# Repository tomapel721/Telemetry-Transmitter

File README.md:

## :book: Long story short
The transmitter part of telemetry system which was implemented inside a Formula Student EV.

## :computer: How it works - technologies
PCB Design: **KiCad**

Project source code: **C (C18) with usage of HAL libraries**
Board used: **STM32L432KC**

## :file_folder: Repository structure
In main directory, you can find 2 folders:
- directory **PCBDesign** contains project of printed circuit used as HW part of the telemetry transmitter
- directory **SourceCode** contains the SW part of the project

## :scroll: How to use my code
Usage of the code can be hard to do, but in case you want to make your own racing car, here is the brief manual:
1. Print the PCB using the _GERBER_ files
2. Solder the board elements
3. Connect soldered electronics to PC
4. Flash the STM32 using ST-LINK debugger (pins where to connect are marked on the PCB schema)
5. Enjoy;)

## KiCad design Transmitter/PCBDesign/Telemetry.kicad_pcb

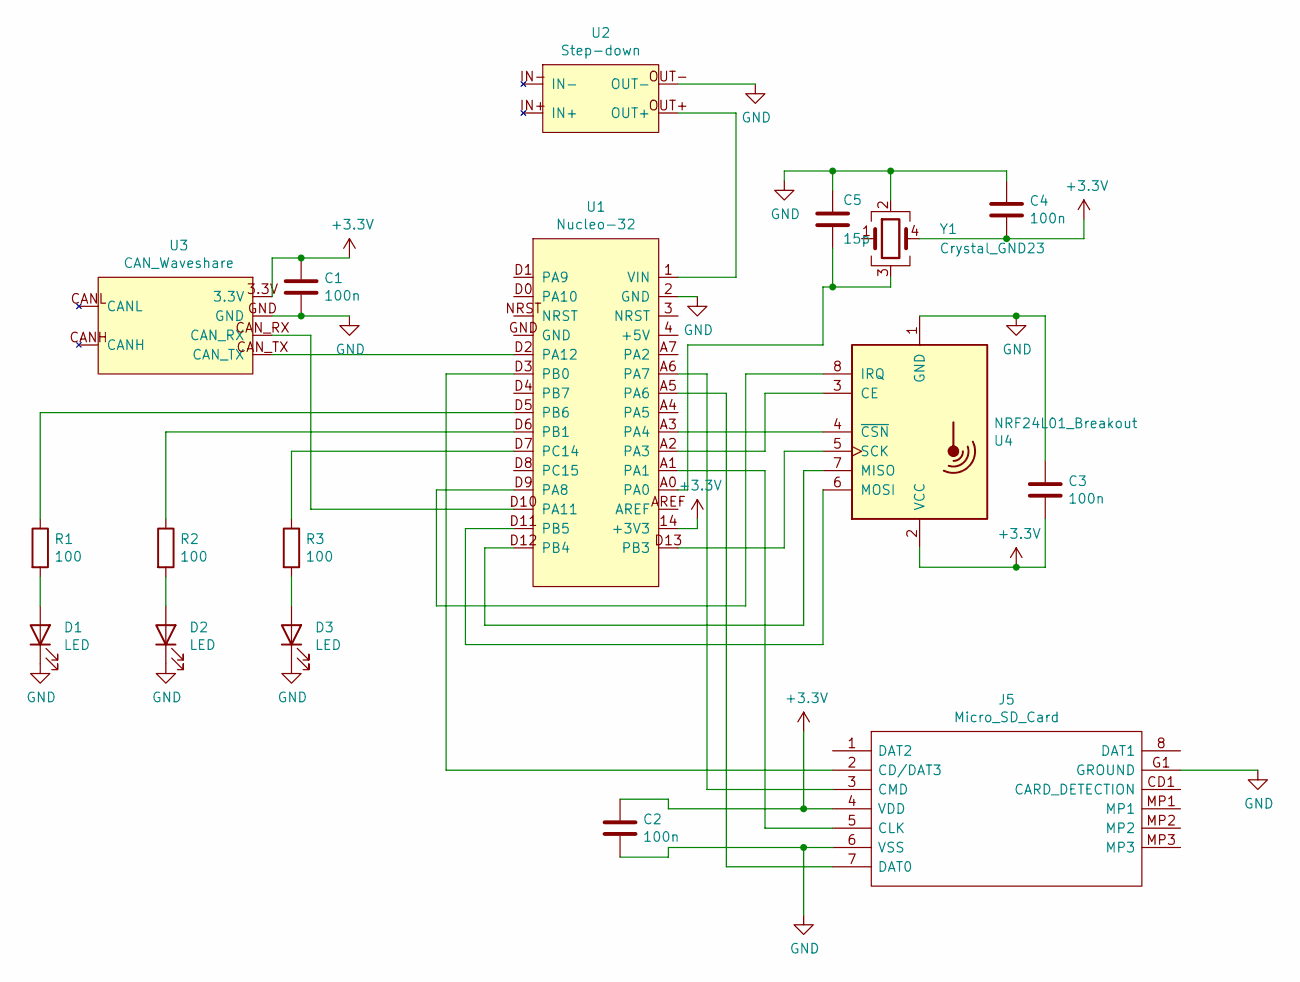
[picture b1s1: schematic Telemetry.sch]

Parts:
C1, C2, C3, C4: 100n; C_0805_2012Metric
C5: 15p; C_0805_2012Metric
D1, D2, D3: LED; D_0805_2012Metric_Pad1.15x1.40mm_HandSolder
J5: Micro_SD_Card; 112JTDARR01; Manufacturer_Part_Number 112J-TDAR-R01
R1, R2, R3: 100; R_0805_2012Metric_Pad1.20x1.40mm_HandSolder
U1: Nucleo-32; Arduino_Nano
U2: Step-down; TerminalBlock_RND_205-00012_1x02_P5.00mm_Horizontal
U3: CAN_Waveshare; PinHeader_1x04_P2.54mm_Vertical
U4: NRF24L01_Breakout; nRF24L01_Breakout
Y1: Crystal_GND23; Crystal_SMD_7050-4Pin_7.0x5.0mm

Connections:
+3V3: C1.1, C2.1, C3.2, C4.2, J5.4 (VDD), U1.14 (+3V3), U3.3.3V, U4.2 (VCC), Y1.4
GND: C1.2, C2.2, C3.1, C4.1, C5.1, D1.1 (K), D2.1 (K), D3.1 (K), J5.6 (VSS), J5.G1 (GROUND), U1.2 (GND), U2.OUT-, U3.GND, U4.1 (GND), Y1.2
unnamed: C5.2, U1.A0, Y1.3
unnamed: D1.2 (A), R1.2
unnamed: D2.2 (A), R2.2
unnamed: D3.2 (A), R3.2
unnamed: J5.2 (CD/DAT3), U1.D3 (PB0)
unnamed: J5.3 (CMD), U1.A6 (PA7)
unnamed: J5.5 (CLK), U1.A1
unnamed: J5.7 (DAT0), U1.A5 (PA6)
unnamed: R1.1, U1.D5 (PB6)
unnamed: R2.1, U1.D6 (PB1)
unnamed: R3.1, U1.D7 (PC14)
unnamed: U1.1 (VIN), U2.OUT+
unnamed: U1.A2 (PA3), U4.3 (CE)
unnamed: U1.A3 (PA4), U4.4 (~CSN)
unnamed: U1.D2 (PA12), U3.CAN_TX
unnamed: U1.D9 (PA8), U4.8 (IRQ)
unnamed: U1.D10 (PA11), U3.CAN_RX
unnamed: U1.D11 (PB5), U4.6 (MOSI)
unnamed: U1.D12 (PB4), U4.7 (MISO)
unnamed: U1.D13 (PB3), U4.5 (SCK)

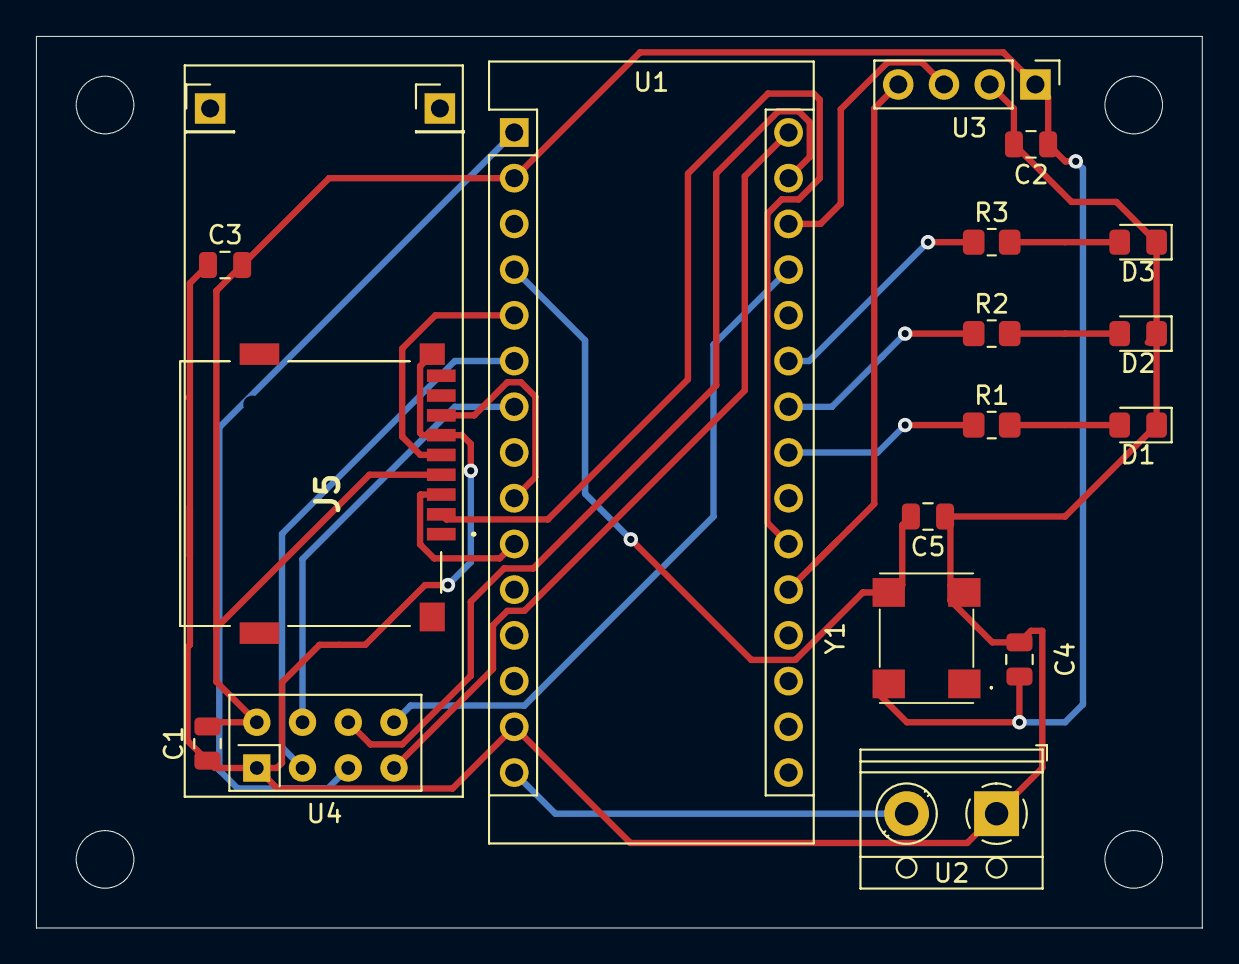
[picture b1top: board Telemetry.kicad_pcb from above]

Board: 2 copper layers, 64.8 x 49.5 mm, 23 parts (0 on the bottom side), 22 nets.

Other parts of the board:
 : .; PinHeader_1x01_P2.54mm_Vertical
 #2: .; PinHeader_1x01_P2.54mm_Vertical
 #3,  #4,  #5,  #6: M3; MountingHole_3.2mm_M3_DIN965

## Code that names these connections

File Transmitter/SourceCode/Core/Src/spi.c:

/**
  ******************************************************************************
  * @file    spi.c
  * @brief   This file provides code for the configuration
  *          of the SPI instances.
  ******************************************************************************
  * @attention
  *
  * <h2><center>&copy; Copyright (c) 2021 STMicroelectronics.
  * All rights reserved.</center></h2>
  *
  * This software component is licensed by ST under Ultimate Liberty license
  * SLA0044, the "License"; You may not use this file except in compliance with
  * the License. You may obtain a copy of the License at:
  *                             www.st.com/SLA0044
  *
  ******************************************************************************
  */

/* Includes ------------------------------------------------------------------*/
#include "spi.h"

/* USER CODE BEGIN 0 */

/* USER CODE END 0 */

SPI_HandleTypeDef hspi1;
SPI_HandleTypeDef hspi3;

/* SPI1 init function */
void MX_SPI1_Init(void)
{

  /* USER CODE BEGIN SPI1_Init 0 */

  /* USER CODE END SPI1_Init 0 */

  /* USER CODE BEGIN SPI1_Init 1 */

  /* USER CODE END SPI1_Init 1 */
  hspi1.Instance = SPI1;
  hspi1.Init.Mode = SPI_MODE_MASTER;
  hspi1.Init.Direction = SPI_DIRECTION_2LINES;
  hspi1.Init.DataSize = SPI_DATASIZE_8BIT;
  hspi1.Init.CLKPolarity = SPI_POLARITY_LOW;
  hspi1.Init.CLKPhase = SPI_PHASE_1EDGE;
  hspi1.Init.NSS = SPI_NSS_SOFT;
  hspi1.Init.BaudRatePrescaler = SPI_BAUDRATEPRESCALER_32;
  hspi1.Init.FirstBit = SPI_FIRSTBIT_MSB;
  hspi1.Init.TIMode = SPI_TIMODE_DISABLE;
  hspi1.Init.CRCCalculation = SPI_CRCCALCULATION_DISABLE;
  hspi1.Init.CRCPolynomial = 7;
  hspi1.Init.CRCLength = SPI_CRC_LENGTH_DATASIZE;
  hspi1.Init.NSSPMode = SPI_NSS_PULSE_ENABLE;
  if (HAL_SPI_Init(&hspi1) != HAL_OK)
  {
    Error_Handler();
  }
  /* USER CODE BEGIN SPI1_Init 2 */

  /* USER CODE END SPI1_Init 2 */

}
/* SPI3 init function */
void MX_SPI3_Init(void)
{

  /* USER CODE BEGIN SPI3_Init 0 */

  /* USER CODE END SPI3_Init 0 */

  /* USER CODE BEGIN SPI3_Init 1 */

  /* USER CODE END SPI3_Init 1 */
  hspi3.Instance = SPI3;
  hspi3.Init.Mode = SPI_MODE_MASTER;
  hspi3.Init.Direction = SPI_DIRECTION_2LINES;
  hspi3.Init.DataSize = SPI_DATASIZE_8BIT;
  hspi3.Init.CLKPolarity = SPI_POLARITY_LOW;
  hspi3.Init.CLKPhase = SPI_PHASE_1EDGE;
  hspi3.Init.NSS = SPI_NSS_SOFT;
  hspi3.Init.BaudRatePrescaler = SPI_BAUDRATEPRESCALER_32;
  hspi3.Init.FirstBit = SPI_FIRSTBIT_MSB;
  hspi3.Init.TIMode = SPI_TIMODE_DISABLE;
  hspi3.Init.CRCCalculation = SPI_CRCCALCULATION_DISABLE;
  hspi3.Init.CRCPolynomial = 7;
  hspi3.Init.CRCLength = SPI_CRC_LENGTH_DATASIZE;
  hspi3.Init.NSSPMode = SPI_NSS_PULSE_ENABLE;
  if (HAL_SPI_Init(&hspi3) != HAL_OK)
  {
    Error_Handler();
  }
  /* USER CODE BEGIN SPI3_Init 2 */

  /* USER CODE END SPI3_Init 2 */

}

void HAL_SPI_MspInit(SPI_HandleTypeDef* spiHandle)
{

  GPIO_InitTypeDef GPIO_InitStruct = {0};
  if(spiHandle->Instance==SPI1)
  {
  /* USER CODE BEGIN SPI1_MspInit 0 */

  /* USER CODE END SPI1_MspInit 0 */
    /* SPI1 clock enable */
    __HAL_RCC_SPI1_CLK_ENABLE();

    __HAL_RCC_GPIOA_CLK_ENABLE();
    /**SPI1 GPIO Configuration
    PA1     ------> SPI1_SCK
    PA6     ------> SPI1_MISO
    PA7     ------> SPI1_MOSI
    */
    GPIO_InitStruct.Pin = GPIO_PIN_1|GPIO_PIN_6|GPIO_PIN_7;
    GPIO_InitStruct.Mode = GPIO_MODE_AF_PP;
    GPIO_InitStruct.Pull = GPIO_NOPULL;
    GPIO_InitStruct.Speed = GPIO_SPEED_FREQ_VERY_HIGH;
    GPIO_InitStruct.Alternate = GPIO_AF5_SPI1;
    HAL_GPIO_Init(GPIOA, &GPIO_InitStruct);

  /* USER CODE BEGIN SPI1_MspInit 1 */

  /* USER CODE END SPI1_MspInit 1 */
  }
  else if(spiHandle->Instance==SPI3)
  {
  /* USER CODE BEGIN SPI3_MspInit 0 */

  /* USER CODE END SPI3_MspInit 0 */
    /* SPI3 clock enable */
    __HAL_RCC_SPI3_CLK_ENABLE();

    __HAL_RCC_GPIOB_CLK_ENABLE();
    /**SPI3 GPIO Configuration
    PB3 (JTDO-TRACESWO)     ------> SPI3_SCK
    PB4 (NJTRST)     ------> SPI3_MISO
    PB5     ------> SPI3_MOSI
    */
    GPIO_InitStruct.Pin = GPIO_PIN_3|GPIO_PIN_4|GPIO_PIN_5;
    GPIO_InitStruct.Mode = GPIO_MODE_AF_PP;
    GPIO_InitStruct.Pull = GPIO_NOPULL;
    GPIO_InitStruct.Speed = GPIO_SPEED_FREQ_VERY_HIGH;
    GPIO_InitStruct.Alternate = GPIO_AF6_SPI3;
    HAL_GPIO_Init(GPIOB, &GPIO_InitStruct);

  /* USER CODE BEGIN SPI3_MspInit 1 */

  /* USER CODE END SPI3_MspInit 1 */
  }
}

void HAL_SPI_MspDeInit(SPI_HandleTypeDef* spiHandle)
{

  if(spiHandle->Instance==SPI1)
  {
  /* USER CODE BEGIN SPI1_MspDeInit 0 */

  /* USER CODE END SPI1_MspDeInit 0 */
    /* Peripheral clock disable */
    __HAL_RCC_SPI1_CLK_DISABLE();

    /**SPI1 GPIO Configuration
    PA1     ------> SPI1_SCK
    PA6     ------> SPI1_MISO
    PA7     ------> SPI1_MOSI
    */
    HAL_GPIO_DeInit(GPIOA, GPIO_PIN_1|GPIO_PIN_6|GPIO_PIN_7);

  /* USER CODE BEGIN SPI1_MspDeInit 1 */

  /* USER CODE END SPI1_MspDeInit 1 */
  }
  else if(spiHandle->Instance==SPI3)
  {
  /* USER CODE BEGIN SPI3_MspDeInit 0 */

  /* USER CODE END SPI3_MspDeInit 0 */
    /* Peripheral clock disable */
    __HAL_RCC_SPI3_CLK_DISABLE();

    /**SPI3 GPIO Configuration
    PB3 (JTDO-TRACESWO)     ------> SPI3_SCK
    PB4 (NJTRST)     ------> SPI3_MISO
    PB5     ------> SPI3_MOSI
    */
    HAL_GPIO_DeInit(GPIOB, GPIO_PIN_3|GPIO_PIN_4|GPIO_PIN_5);

  /* USER CODE BEGIN SPI3_MspDeInit 1 */

  /* USER CODE END SPI3_MspDeInit 1 */
  }
}

/* USER CODE BEGIN 1 */

/* USER CODE END 1 */

/************************ (C) COPYRIGHT STMicroelectronics *****END OF FILE****/

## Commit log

2025-02-05 Upload latest files
2026-01-17 Code refactoring
    - Fixed application code warning on -Wextra and -pedantic level
    - Improved code structure
    * Introduced new dir for SD related files
    - Fixed magic numbers
    - Slight optimization in arguments passed to functions
